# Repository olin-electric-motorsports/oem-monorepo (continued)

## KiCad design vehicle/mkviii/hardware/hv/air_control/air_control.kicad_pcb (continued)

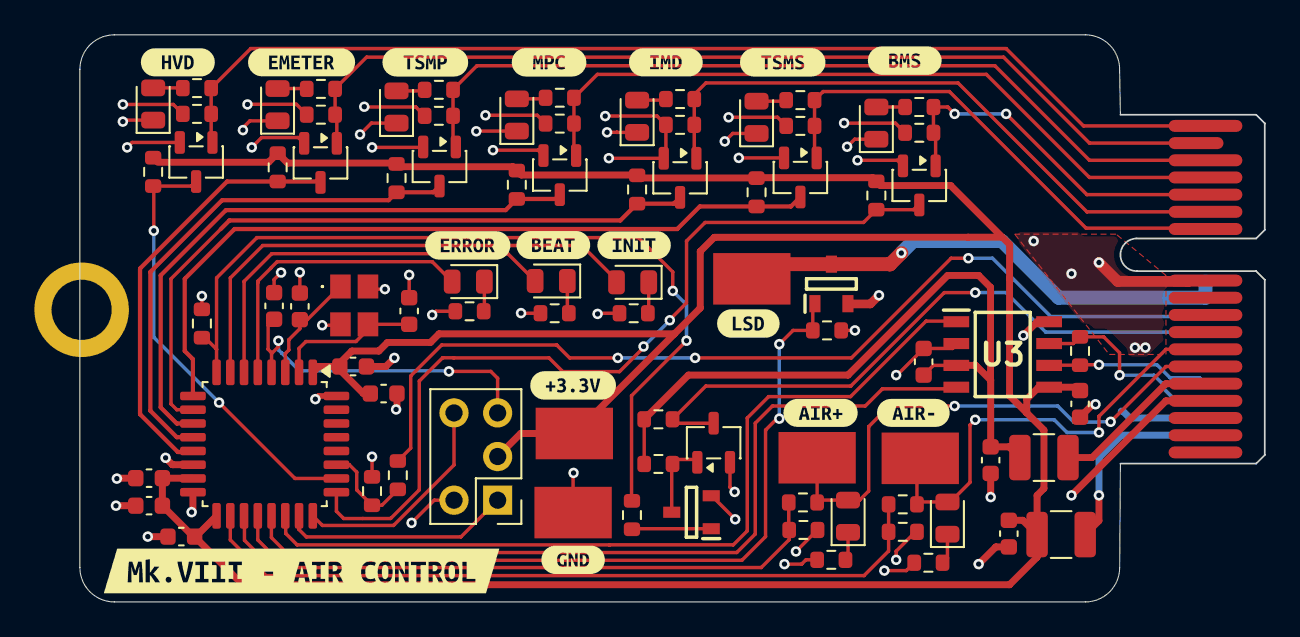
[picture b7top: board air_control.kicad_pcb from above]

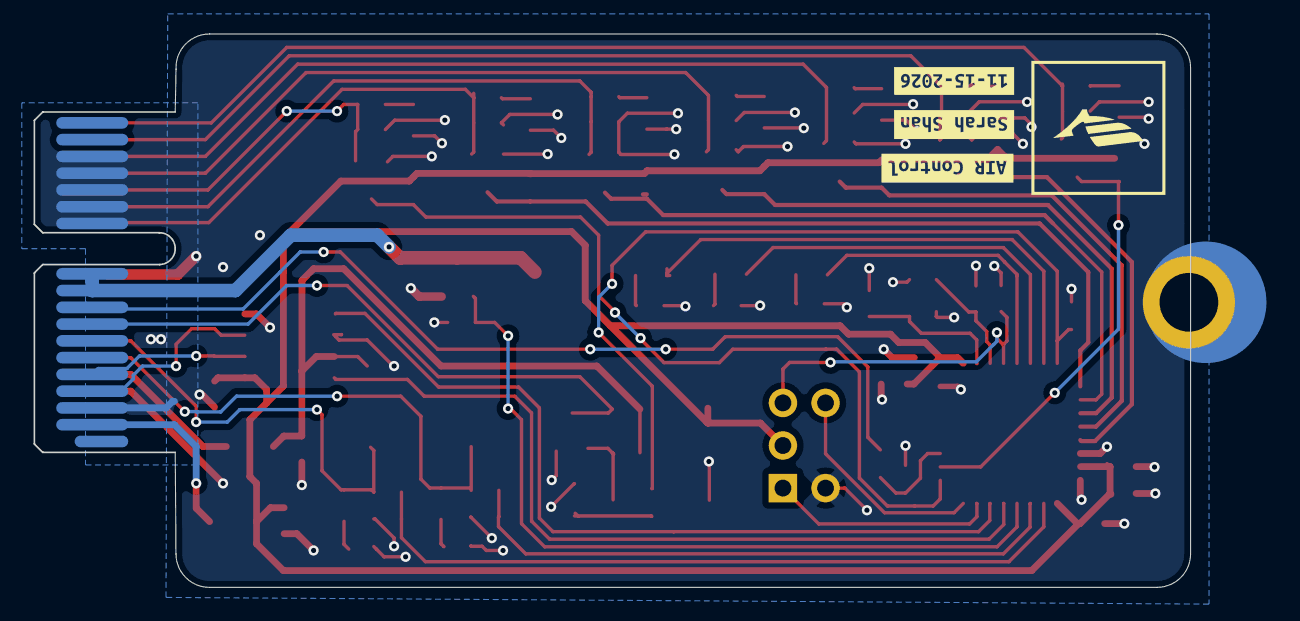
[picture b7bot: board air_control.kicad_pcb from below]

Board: 2 copper layers, 68.9 x 33.0 mm, 104 parts (3 on the bottom side), 55 nets.

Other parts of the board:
kibuzzard-6AF9317E: G***; kibuzzard-6AF9317E
kibuzzard-6AFA4FF6: G***; kibuzzard-6AFA4FF6
kibuzzard-6AFA20AB: G***; kibuzzard-6AFA20AB
kibuzzard-6AFA20E3: G***; kibuzzard-6AFA20E3
kibuzzard-6AFA20FC: G***; kibuzzard-6AFA20FC
kibuzzard-6AFA21A2: G***; kibuzzard-6AFA21A2
kibuzzard-6AFA21B3: G***; kibuzzard-6AFA21B3
kibuzzard-6AFA22A9: G***; kibuzzard-6AFA22A9
kibuzzard-6AFA27BC: G***; kibuzzard-6AFA27BC
kibuzzard-6AFA208A: G***; kibuzzard-6AFA208A
kibuzzard-6AFA210D: G***; kibuzzard-6AFA210D
kibuzzard-6AFA219C: G***; kibuzzard-6AFA219C
kibuzzard-6AFA2118: G***; kibuzzard-6AFA2118
kibuzzard-6AFA2276: G***; kibuzzard-6AFA2276
kibuzzard-6AFA2289: G***; kibuzzard-6AFA2289
kibuzzard-6AFA2297: G***; kibuzzard-6AFA2297
kibuzzard-6AFA2756: G***; kibuzzard-6AFA2756
kibuzzard-6AFA2784: G***; kibuzzard-6AFA2784
kibuzzard-6AFDC125: G***; kibuzzard-6AFDC125

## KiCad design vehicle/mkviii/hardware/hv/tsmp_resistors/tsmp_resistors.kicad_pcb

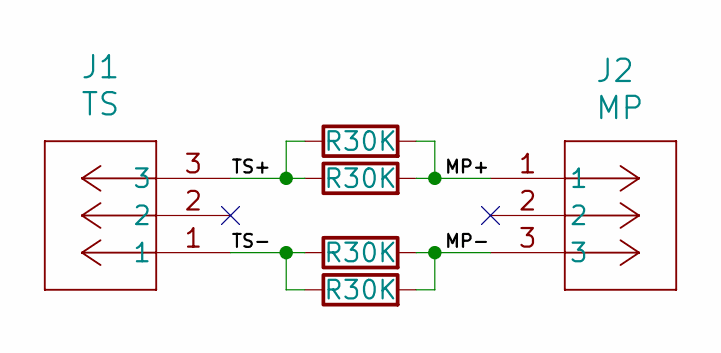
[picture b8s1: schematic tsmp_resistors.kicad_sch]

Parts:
J1: TS; J_Molex_Header_01x03_VT
J2: MP; J_Molex_Header_01x03_VT
R1, R2, R3, R4: R30K; R_5329_13573Metric; MPN SMF530KJT

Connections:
/MP+: J2.1, R1.2, R2.2
/MP-: J2.3, R3.2, R4.2
/TS+: J1.3, R1.1, R2.1
/TS-: J1.1, R3.1, R4.1

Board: 2 copper layers, 9 parts (3 on the bottom side), 4 nets, no tracks yet.

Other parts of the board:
kibuzzard-6B01073E: G***; kibuzzard-6B01073E
kibuzzard-6B01079E: G***; kibuzzard-6B01079E
kibuzzard-6B010778: G***; kibuzzard-6B010778

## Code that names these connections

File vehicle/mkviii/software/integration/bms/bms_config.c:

#include "bms_config.h"
#include "stm32g4xx_hal_tim.h"

TIM_HandleTypeDef htim2; // Fan PWM

/*
 * PIN DEFINITIONS
 */
// GPIO Setup
void GpioInit(void){
    // enable clocks for ports we are using
    __HAL_RCC_GPIOA_CLK_ENABLE();
    __HAL_RCC_GPIOB_CLK_ENABLE();

    // generic structure
    GPIO_InitTypeDef GPIO_InitStruct = {0};

    // port A outputs: relay drive and LEDs
    HAL_GPIO_WritePin(GPIOA, BMS_RELAY_DRIVE_PIN | HEARTBEAT_PIN | ERROR_LED_PIN | CSC_COMMS_PIN, GPIO_PIN_RESET);
    GPIO_InitStruct.Pin = BMS_RELAY_DRIVE_PIN | HEARTBEAT_PIN | ERROR_LED_PIN | CSC_COMMS_PIN;
    GPIO_InitStruct.Mode = GPIO_MODE_OUTPUT_PP;
    GPIO_InitStruct.Pull = GPIO_NOPULL;
    GPIO_InitStruct.Speed = GPIO_SPEED_FREQ_LOW;
    HAL_GPIO_Init(GPIOA, &GPIO_InitStruct);

    // configure port A inputs
    // BSPD_CURRENT_THRESH (PA9), driven by U7 so no pull needed
    GPIO_InitStruct.Pin = BSPD_CURRENT_THRESH_PIN;
    GPIO_InitStruct.Mode = GPIO_MODE_INPUT;
    GPIO_InitStruct.Pull = GPIO_NOPULL;
    HAL_GPIO_Init(BSPD_CURRENT_THRESH_PORT, &GPIO_InitStruct);

    // Fan PWM (PA0) is TIM2_CH1
    GPIO_InitStruct.Pin = FAN_PWM_PIN;
    GPIO_InitStruct.Mode = GPIO_MODE_AF_PP;
    GPIO_InitStruct.Pull = GPIO_NOPULL;
    GPIO_InitStruct.Speed = GPIO_SPEED_FREQ_LOW;
    GPIO_InitStruct.Alternate = GPIO_AF1_TIM2;
    HAL_GPIO_Init(FAN_PWM_PORT, &GPIO_InitStruct);

    // ISO_CS (PA15) and the SPI1 pins (PB3-PB5) are set up by oem_spi_init()
}

// timer initialization
void TimerInit(void) {
    // --- Timer 2: 25kHz fan PWM on CH1 ---
    // The 10ms main loop runs off HAL_GetTick() instead of a timer interrupt
    // because common/startup.c's vector table has no peripheral IRQ entries.
    __HAL_RCC_TIM2_CLK_ENABLE();

    htim2.Instance = TIM2;
    htim2.Init.Prescaler = 0;
    htim2.Init.CounterMode = TIM_COUNTERMODE_UP;
    htim2.Init.Period = (HAL_RCC_GetPCLK1Freq() / FAN_PWM_FREQ_HZ) - 1;
    htim2.Init.ClockDivision = TIM_CLOCKDIVISION_DIV1;
    htim2.Init.AutoReloadPreload = TIM_AUTORELOAD_PRELOAD_ENABLE;
    HAL_TIM_PWM_Init(&htim2);

    TIM_OC_InitTypeDef sConfigOC = {0};
    sConfigOC.OCMode = TIM_OCMODE_PWM1;
    sConfigOC.Pulse = 0;
    sConfigOC.OCPolarity = TIM_OCPOLARITY_HIGH;
    sConfigOC.OCFastMode = TIM_OCFAST_DISABLE;
    HAL_TIM_PWM_ConfigChannel(&htim2, &sConfigOC, TIM_CHANNEL_1);
}

// FDCAN1 on PA11 (RX) / PA12 (TX). Called by HAL_FDCAN_Init() from the
// generated can_init_bms(). The generated bit timing assumes the FDCAN kernel
// clock is the 16MHz HSE, which is the reset default.
void HAL_FDCAN_MspInit(FDCAN_HandleTypeDef* hfdcan) {
    if (hfdcan->Instance == FDCAN1) {
        __HAL_RCC_FDCAN_CLK_ENABLE();
        __HAL_RCC_GPIOA_CLK_ENABLE();

        GPIO_InitTypeDef GPIO_InitStruct = {0};
        GPIO_InitStruct.Pin = GPIO_PIN_11 | GPIO_PIN_12;
        GPIO_InitStruct.Mode = GPIO_MODE_AF_PP;
        GPIO_InitStruct.Pull = GPIO_NOPULL;
        GPIO_InitStruct.Speed = GPIO_SPEED_FREQ_LOW;
        GPIO_InitStruct.Alternate = GPIO_AF9_FDCAN1;
        HAL_GPIO_Init(GPIOA, &GPIO_InitStruct);
    }
}

// Defined in the generated can_api.c
extern FDCAN_HandleTypeDef hfdcan1;

void can_wait_for_tx_slot(void) {
    uint32_t start = HAL_GetTick();
    while (HAL_FDCAN_GetTxFifoFreeLevel(&hfdcan1) == 0
           && (HAL_GetTick() - start) < 2) {
    }
}

// interupt handlers
void SysTick_Handler(void) {
    HAL_IncTick(); // Critical for HAL_Delay() and HAL_GetTick() to work!
}

// ISO_CS is PA15, SPI1 is PB3 (SCK), PB4 (MISO), PB5 (MOSI).
// The LTC6820 has POL = PHA = 1 (SPI mode 3, matches common/spi) and SLOW = 0,
// so SCK must stay at or below 1MHz: 64MHz / 128 = 500kHz.
oem_spi_config_t bms_spi = {
    .spi_instance = SPI1,
    .cs_port = ISO_CS_PORT,
    .cs_pin = ISO_CS_PIN,
    .baud_prescaler = SPI_BAUDRATEPRESCALER_128
};

// ADC CONFIGURATION

// Current sensor output, divided down by R2/R4, on PA4 (ADC2_IN17)
oem_adc_config_t current_sense_vout = {
    .adc_instance = ADC2,
    .port = VOUT_CURRENT_SENSE_PORT,
    .pin = VOUT_CURRENT_SENSE_PIN,
    .channel = ADC_CHANNEL_17,
    .sample_time = ADC_SAMPLETIME_47CYCLES_5
};

cell_data_s cell_data = {0};

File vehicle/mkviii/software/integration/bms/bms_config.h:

#pragma once

#include <stdbool.h>       // For bool, true, false
#include <stdint.h>        // For uint8_t, int16_t, etc.
#include "stm32g4xx_hal.h" // The master STM32 HAL header

#include "common/adc/adc.h"
#include "common/spi/spi.h"

#include "vehicle/common/adbms1818/ADBMS181x.h"

// Pin Defs
// Taken from the U10 pads in hardware/integration/bms_core/bms_core.kicad_pcb
// (STM32G441KBT6, LQFP-32). PA1-PA3, PA10, PB0 and PB6-PB8 are unconnected.
// Port A
#define FAN_PWM_PIN              GPIO_PIN_0  // pin 5,  TIM2_CH1 (AF1)
#define FAN_PWM_PORT             GPIOA
#define VOUT_CURRENT_SENSE_PIN   GPIO_PIN_4  // pin 9,  ADC2_IN17, via 5.1k/10k divider
#define VOUT_CURRENT_SENSE_PORT  GPIOA
#define ERROR_LED_PIN            GPIO_PIN_5  // pin 10, red LED D3
#define ERROR_LED_PORT           GPIOA
#define CSC_COMMS_PIN            GPIO_PIN_6  // pin 11, green LED D2
#define CSC_COMMS_PORT           GPIOA
#define HEARTBEAT_PIN            GPIO_PIN_7  // pin 12, amber LED D1
#define HEARTBEAT_PORT           GPIOA
#define BMS_RELAY_DRIVE_PIN      GPIO_PIN_8  // pin 18, gate of Q1
#define BMS_RELAY_DRIVE_PORT     GPIOA
#define BSPD_CURRENT_THRESH_PIN  GPIO_PIN_9  // pin 19, output of U7
#define BSPD_CURRENT_THRESH_PORT GPIOA
#define ISO_CS_PIN               GPIO_PIN_15 // pin 25, LTC6820 ~CS
#define ISO_CS_PORT              GPIOA

// Port B
// ISO_SCK (PB3), ISO_MISO (PB4), ISO_MOSI (PB5) are SPI1 and are configured by
// oem_spi_init() in common/spi. Do not use PB3 as a GPIO.

extern TIM_HandleTypeDef htim2; // Fan PWM
#define FAN_PWM_FREQ_HZ (25000)

void TimerInit(void); // Function prototype to set them up

/*
 * Wait (up to 2ms) for a free slot in the FDCAN TX FIFO. The FIFO only holds 3
 * frames, so call this before each can_send_*() when sending several messages
 * back to back.
 */
void can_wait_for_tx_slot(void);

/*
 * Macros
 */
#define NUM_ICS          1

#define MAX_EXTRANEOUS_TEMPERATURES 3 // causing isssssueeeess... maybe set to higher value - ian W 9/14/2024
#define MAX_PEC_ERROR_COUNT \
    32 // copied from mkv where it still says arbitrary...

// copied from MKV - need to be updated
#define FAKE_DA_FIRE_BODGE                 ((int16_t)700) // 140 degC
#define OVERTEMPERATURE_THRESHOLD          ((int16_t)5725) // 60 degC
#define SOFT_OVERTEMPERATURE_THRESHOLD     ((int16_t)8892) // 45 degC
#define SOFT_OVERTEMPERATURE_THRESHOLD_LOW ((int16_t)11708) // 35 degC
#define UNDERTEMPERATURE_THRESHOLD         ((int16_t)27605) // -20 degC

// Cell voltage codes are in units of 100uV
#define OVERVOLTAGE_THRESHOLD          (42000) // 4.2V
#define UNDERVOLTAGE_THRESHOLD         (25000) // 2.5V (Li-ion chemistry minimum)
#define SEGMENT_OVERVOLTAGE_THRESHOLD  (714000) // 71.4V (4.2v * 17 cells)
#define SEGMENT_UNDERVOLTAGE_THRESHOLD (442000) // 44.2V (4.6 * 17 cells)

#define CURRENT_THRESH (12000) // 120A (peak current) * 100cA/A = 12,000 centiAmps

/*
 * Current sensor calibration. The sensor output (0-5V) goes through a
 * 5.1k/10k divider into PA4, so the sensor voltage is V_pin * 15.1 / 10.
 * CURRENT_SENSE_ZERO_MV is the sensor output at 0A. 2773mV is the zero point
 * MKVII used (raw 568 on a 10-bit, 5V ADC) - measure it on this car with no
 * current flowing and update.
 */
#define CURRENT_SENSE_ZERO_MV  (2773)
#define CURRENT_SENSE_MV_PER_A (20)

// Open wire: a cell is open if (pull-up reading - pull-down reading) is above
// this, in 100uV units. 4000 = 400mV, from the ADBMS181x reference driver.
#define OPEN_WIRE_THRESHOLD (4000)

// Cell balancing config
// Balance any cell more than this above the lowest cell (100uV units)
#define BALANCE_THRESHOLD (100) // 10mV
// Discharge timeout written to DCTO in CFGRA. Balancing switches turn off on
// their own if the BMS stops refreshing the config (0x1 = 0.5 minutes)
#define BALANCE_DCTO (0x1)

// ADBMS1818 internal die temperature, ITMP code in 100uV units.
// T(degC) = ITMP * 100uV / 7.6mV - 276, so 85degC -> (85 + 276) * 76 = 27436
#define DIE_OVERTEMPERATURE_THRESHOLD (27436)

// Number (out of 18) voltage channels not used. Unused channels are bridged
// and read as 0V
#define NUM_UNUSED_VOLTAGE_CHANNELS 1

/*
 * PIN & PERIPHERAL DEFINITIONS
 */
void GpioInit(void);

// 04/13/26
//SPI Peripheral Configuration
extern oem_spi_config_t bms_spi;

/** 04/18/26
 * ADC Configurations
 * Mapped to the STM32G4 ADC
 */
extern oem_adc_config_t current_sense_vout; // Mapped to PA4

// A little bit of a hacky, truncated version of the cell_asic
// struct defined by the LTC681X library. Filled by voltage_task() and used for
// cell balancing.
typedef struct {
    ic_register config;
    cv cells;
} cell_asic_trunc;

typedef struct {
    cell_asic_trunc cells[NUM_ICS];
} cell_data_s;

extern cell_data_s cell_data;

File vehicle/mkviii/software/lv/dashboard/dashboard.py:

###### DO NOT USE THIS CODE ######
#UPLOAD SCRIPT FROM THE CAR


import os
import threading
import time
import cantools
import can
import RPi.GPIO as GPIO

BUSTYPE = "socketcan"
CHANNEL = "can0"
BITRATE = 500000

# Loading in everyone's compiled config files
# (mkvi.dbc is deployed next to this file, see deploy/config.json)
dbc_file = os.path.join(os.path.dirname(os.path.abspath(__file__)), "mkvi.dbc")
db = cantools.database.load_file(dbc_file)

# Making variables that store incoming CAN data global
air_state = "INIT"
imd_status = "IMD OK"
bms_state = "ACTIVE"
brake_gate = "Brakelight OFF"
throttle_pressed = False

# Pin Definitions
BMS_LED_LSD = 36
HV_LED_LSD = 29
IMD_LED_LSD = 16  # 26 IAN W changing this 6/9/24
RTD_BUZZER_LSD = 32

RTD_BUTTON_SENSE = 31
BOTS_SHDN_SENSE = 18
E_STOP_SHDN_SENSE = 22

RTD_BUTTON_LED = 33
PROGRAMMING_LED_1 = 40
PROGRAMMING_LED_2 = 38
PROGRAMMING_LED_3 = 37

# Number of seconds the buzzer sounds
RTD_BUZZ_TIME = 2000  # in milliseconds

# Initializing the dictionary that holds outgoing CAN data
dashboard_data = {"ready_to_drive": False, "start_button_state": False, "ss_estop": False, "ss_bots": False, }


def init_can(channel, bustype, bitrate, callback):
    """Initialize CAN hardware and create CAN database from DBC
    Args:
        channel: port or network interface on the
                 Raspi the CAN single is connected to
        bustype: Type of CAN interface/dongle
        bitrate: Bus speed in Kbps

    """
    can_bus = can.interface.Bus(
        channel=channel,
        bustype=bustype,
        bitrate=bitrate,
    )

    kill_flag = threading.Event()
    listener = threading.Thread(
        target=dashboard_listener,
        name="listener",
        kwargs={"can_bus": can_bus, "callback": callback, "kill_flag": kill_flag},
    )

    listener.start()
    return can_bus, kill_flag


def dashboard_listener(can_bus, callback, kill_flag):
    """Thread that runs all the time to listen to CAN messages
    References:
      - https://python-can.readthedocs.io/en/master/interfaces/socketcan.html
      - https://python-can.readthedocs.io/en/master/
    """
    while not kill_flag.is_set():
        msg = can_bus.recv(1)  # 1 second receive timeout
        if msg:
            callback(msg, db)

    can_bus.shutdown()
    print("Exited gracefully")


def dashboard_callback(msg, db):
    """
    Callback when a CAN message is received, updates appropriate vehicle
    dictionaries
    Args:
        msg (can.Message): CAN message that was received
        db (cantools.database): Database generated from our DBC
    """
    global air_state, imd_status, bms_state, brake_gate, throttle_pressed

    try:
        message = db.decode_message(msg.arbitration_id, msg.data)
    except Exception as _:
        print("bad message")
        return

    message_name = db.get_message_by_frame_id(msg.arbitration_id).name

    if message_name == "air_control_critical":
        air_state = message.get("air_state")
        imd_status = message.get("imd_status")
    if message_name == "bms_core":
        bms_state = message.get("bms_state")
        print(bms_state)
    if message_name == "bspd":
        brake_gate = message.get("brake_gate") == "Brakelight ON"
    if message_name == "throttle":
        throttle_l = message.get("throttle_l_pos")
        throttle_r = message.get("throttle_r_pos")
        throttle_pressed = throttle_l >= 12 or throttle_r >= 12


# Enabling the start button interrupt
def button_pressed_callback(channel):
    """
    When called, this sets the value of "start_button_state" in the outgoing
    CAN data dictionary (dashboard_data) to True
    """
    dashboard_data["start_button_state"] = GPIO.input(RTD_BUTTON_SENSE)


def shutdown_callback(channel):
    """
    When called, this updates the values of "ss_bots" and "ss_estop" in the
    outgoing CAN data dictionary (dashboard_data) to False

    Args:
        channel: an integer representing a pin number corresponding to either
        the ss_bots or ss_estop pins
    """
    if channel == BOTS_SHDN_SENSE:
        dashboard_data["ss_bots"] = GPIO.input(BOTS_SHDN_SENSE)
    if channel == E_STOP_SHDN_SENSE:
        dashboard_data["ss_estop"] = GPIO.input(E_STOP_SHDN_SENSE)


def main():
    """
    Contains the superloop intended to run every 10 milliseconds;
    Separate thread continually updates relevant variables
    `dashboard_data` is a dictionary containing all outgoing CAN data.
    """
    # Set pin numbering system
    GPIO.setmode(GPIO.BOARD)

    # Channel Setup/Pin Mode Setup
    channel_outputs = [
        BMS_LED_LSD,
        HV_LED_LSD,
        IMD_LED_LSD,
        RTD_BUZZER_LSD,
        RTD_BUTTON_LED,
        PROGRAMMING_LED_1,
        PROGRAMMING_LED_2,
        PROGRAMMING_LED_3,
    ]

    channel_inputs = [RTD_BUTTON_SENSE, BOTS_SHDN_SENSE, E_STOP_SHDN_SENSE]
    GPIO.setup(channel_outputs, GPIO.OUT)
    GPIO.setup(channel_inputs, GPIO.IN)
    GPIO.output(HV_LED_LSD, 1)
    GPIO.output(IMD_LED_LSD, 1)
    GPIO.output(BMS_LED_LSD, 1)
    time.sleep(.5)
    GPIO.output(HV_LED_LSD, 0)
    GPIO.output(IMD_LED_LSD, 0)
    GPIO.output(BMS_LED_LSD, 0)
    # Initialize a thread to constantly update STATES_DICTIONARY from CAN messages
    can_bus, kill_flag = init_can(CHANNEL, BUSTYPE, BITRATE, dashboard_callback)

    # Adding start button, bots shutdown, and estop shutdown interrupts
    GPIO.add_event_detect(
        RTD_BUTTON_SENSE, GPIO.BOTH, callback=button_pressed_callback, bouncetime=50
    )
    GPIO.add_event_detect(BOTS_SHDN_SENSE, GPIO.RISING, callback=shutdown_callback)
    GPIO.add_event_detect(E_STOP_SHDN_SENSE, GPIO.RISING, callback=shutdown_callback)
    #GPIO.output(IMD_LED_LSD, 1)
    buzzer_counter = 0  # buzzer_counter starts at 0

    dashboard_message = db.get_message_by_name("dashboard")

    button_pressed_callback(RTD_BUTTON_SENSE)
    shutdown_callback(BOTS_SHDN_SENSE)
    shutdown_callback(E_STOP_SHDN_SENSE)
    #GPIO.output(BMS_LED_LSD, 1)

    while True:  # MAKE THIS RUN EVERY 10 MILLISECONDS
        t_0 = time.perf_counter()

        # Turns on BMS LED if there are any BMS faults
        GPIO.output(PROGRAMMING_LED_1, bms_state != "ACTIVE")
        GPIO.output(BMS_LED_LSD, bms_state != "ACTIVE")

        # Turns on HV LED if the tractive system is on
        GPIO.output(HV_LED_LSD, air_state == "TS_ACTIVE")

        # Turns on IMD LED if there is an IMD fault; imd_status True is good
        GPIO.output(IMD_LED_LSD, imd_status != "IMD OK")

        # Turns on the button LED if brakes are pressed, tractive system is on,
        # RTD is not on, and the throttle is not being pressed
        if (
            brake_gate
            and air_state == "TS_ACTIVE"
            and not dashboard_data["ready_to_drive"]
            and not throttle_pressed
        ):
            GPIO.output(RTD_BUTTON_LED, 1)  # Turn on button LED
        else:
            GPIO.output(RTD_BUTTON_LED, 0)

        # Update "ready_to_drive", turn off the button LED and start the buzzer
        # Set the counter to 0 to start off with
        if (
            air_state == "TS_ACTIVE"
            and brake_gate
            and dashboard_data["start_button_state"]
            and not throttle_pressed
        ):
            dashboard_data["ready_to_drive"] = True
            GPIO.output(RTD_BUTTON_LED, 0)
            GPIO.output(RTD_BUZZER_LSD, 1)

        # Turn off the button LED and RTD false in dicts if tractive system not active
        # Also reset the buzzer
        if air_state != "TS_ACTIVE":
            GPIO.output(RTD_BUTTON_LED, 0)  # Turn off button LED
            dashboard_data["ready_to_drive"] = False
            buzzer_counter = 0

        # Add 10 milliseconds to the buzzing timer every loop
        if dashboard_data["ready_to_drive"] and buzzer_counter < RTD_BUZZ_TIME:
            buzzer_counter += 10

        if buzzer_counter >= RTD_BUZZ_TIME:
            GPIO.output(RTD_BUZZER_LSD, 0)

        data = dashboard_message.encode(dashboard_data)
        message = can.Message(arbitration_id=dashboard_message.frame_id, data=data, is_extended_id=False)
        can_bus.send(message)  # Send out RTD status over CAN
        
        # Make the loop run every 10 milliseconds
        delta = time.perf_counter() - t_0
        if delta < 0.01:
            time.sleep(0.01 - delta)


# Stores code that should only run when dashboard.py is run as a script and not
# as a module
if __name__ == "__main__":
    main()

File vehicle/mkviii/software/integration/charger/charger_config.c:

#include "charger.h"

/*
 * =========================
 * Timer handle
 * =========================
 */
TIM_HandleTypeDef htim2;

/*
 * =========================
 * SPI configs
 * =========================
 *
 * LCD:
 *   CS   = PA15
 *   SCK  = PB3
 *   MISO = PB4
 *   MOSI = PB5
 *
 * Charger CAN controller:
 *   CS   = PB12
 *   SCK  = PB13
 *   MISO = PB14
 *   MOSI = PB15
 */
oem_spi_config_t lcd_spi = {
    .spi_instance = SPI1,
    .cs_port = LCD_SPI_CS_GPIO_Port,
    .cs_pin = LCD_SPI_CS_Pin,
    .baud_prescaler = SPI_BAUDRATEPRESCALER_16
};

oem_spi_config_t charger_spi = {
    .spi_instance = SPI2,
    .cs_port = CAN_CTRLR_SPI_CS_GPIO_Port,
    .cs_pin = CAN_CTRLR_SPI_CS_Pin,
    .baud_prescaler = SPI_BAUDRATEPRESCALER_64
};

/*
 * If your STM32 MCP25625 wrapper needs this object, uncomment and adapt as needed.
 *
MCP25625 charger_CAN_converter = {
    .speed = 250000,
    .spi_struct = &charger_spi,
    .rst = &(gpio_t){0},
    .stby = &(gpio_t){0}
};
*/

void GpioInit(void) {
    /*
    __HAL_RCC_GPIOA_CLK_ENABLE();
    __HAL_RCC_GPIOB_CLK_ENABLE();
    __HAL_RCC_GPIOC_CLK_ENABLE();
    */

    GPIO_InitTypeDef GPIO_InitStruct = {0};

    /*
     * =========================
     * Status / control output pins
     * =========================
     */
    HAL_GPIO_WritePin(SPI_STATUS_GPIO_Port, SPI_STATUS_Pin, GPIO_PIN_RESET);
    HAL_GPIO_WritePin(CHARGING_STATUS_GPIO_Port, CHARGING_STATUS_Pin, GPIO_PIN_RESET);
    HAL_GPIO_WritePin(FULLY_CHARGED_STATUS_GPIO_Port, FULLY_CHARGED_STATUS_Pin, GPIO_PIN_RESET);
    HAL_GPIO_WritePin(ELCON_READY_GPIO_Port, ELCON_READY_Pin, GPIO_PIN_RESET);
    HAL_GPIO_WritePin(CAR_READY_GPIO_Port, CAR_READY_Pin, GPIO_PIN_RESET);
    HAL_GPIO_WritePin(CHARGING_ON_OFF_STATUS_GPIO_Port, CHARGING_ON_OFF_STATUS_Pin, GPIO_PIN_RESET);
    HAL_GPIO_WritePin(CAN_STATUS_GPIO_Port, CAN_STATUS_Pin, GPIO_PIN_RESET);
    HAL_GPIO_WritePin(HEARTBEAT_GPIO_Port, HEARTBEAT_Pin, GPIO_PIN_RESET);

    /*
     * Port A outputs
     */
    GPIO_InitStruct.Pin = SPI_STATUS_Pin |
                          CHARGING_STATUS_Pin |
                          FULLY_CHARGED_STATUS_Pin |
                          ELCON_READY_Pin |
                          CAR_READY_Pin |
                          CHARGING_ON_OFF_STATUS_Pin |
                          EVSE_PWM_Pin;
    GPIO_InitStruct.Mode = GPIO_MODE_OUTPUT_PP;
    GPIO_InitStruct.Pull = GPIO_NOPULL;
    GPIO_InitStruct.Speed = GPIO_SPEED_FREQ_LOW;
    HAL_GPIO_Init(GPIOA, &GPIO_InitStruct);

    /*
     * Port C outputs
     */
    GPIO_InitStruct.Pin = CAN_STATUS_Pin | HEARTBEAT_Pin;
    GPIO_InitStruct.Mode = GPIO_MODE_OUTPUT_PP;
    GPIO_InitStruct.Pull = GPIO_NOPULL;
    GPIO_InitStruct.Speed = GPIO_SPEED_FREQ_LOW;
    HAL_GPIO_Init(GPIOC, &GPIO_InitStruct);

    /*
     * =========================
     * LCD control pins
     * CS = PA15
     * RST = PB6
     * BLK = PB7
     * =========================
     */


     /*
    HAL_GPIO_WritePin(LCD_SPI_CS_GPIO_Port, LCD_SPI_CS_Pin, GPIO_PIN_SET);
    HAL_GPIO_WritePin(LCD_RST_GPIO_Port, LCD_RST_Pin, GPIO_PIN_SET);
    HAL_GPIO_WritePin(LCD_BLK_GPIO_Port, LCD_BLK_Pin, GPIO_PIN_SET);
    */


    /*
     * LCD CS on PA15
     */
    GPIO_InitStruct.Pin = LCD_SPI_CS_Pin;
    GPIO_InitStruct.Mode = GPIO_MODE_OUTPUT_PP;
    GPIO_InitStruct.Pull = GPIO_NOPULL;
    GPIO_InitStruct.Speed = GPIO_SPEED_FREQ_HIGH;
    HAL_GPIO_Init(GPIOA, &GPIO_InitStruct);

    GPIO_InitStruct.Pin = LCD_RST_Pin | LCD_BLK_Pin;
    GPIO_InitStruct.Mode = GPIO_MODE_OUTPUT_PP;
    GPIO_InitStruct.Pull = GPIO_NOPULL;
    GPIO_InitStruct.Speed = GPIO_SPEED_FREQ_HIGH;
    HAL_GPIO_Init(GPIOB, &GPIO_InitStruct);

    HAL_GPIO_WritePin(CAN_CTRLR_SPI_CS_GPIO_Port, CAN_CTRLR_SPI_CS_Pin, GPIO_PIN_SET);
    HAL_GPIO_WritePin(CAN_CTRLR_RST_GPIO_Port, CAN_CTRLR_RST_Pin, GPIO_PIN_SET);
    HAL_GPIO_WritePin(CHARGER_STBY_GPIO_Port, CHARGER_STBY_Pin, GPIO_PIN_RESET);

    GPIO_InitStruct.Pin = CAN_CTRLR_RST_Pin | CAN_CTRLR_SPI_CS_Pin;
    GPIO_InitStruct.Mode = GPIO_MODE_OUTPUT_PP;
    GPIO_InitStruct.Pull = GPIO_NOPULL;
    GPIO_InitStruct.Speed = GPIO_SPEED_FREQ_HIGH;
    HAL_GPIO_Init(GPIOB, &GPIO_InitStruct);

    GPIO_InitStruct.Pin = CHARGER_STBY_Pin;
    GPIO_InitStruct.Mode = GPIO_MODE_OUTPUT_PP;
    GPIO_InitStruct.Pull = GPIO_NOPULL;
    GPIO_InitStruct.Speed = GPIO_SPEED_FREQ_HIGH;
    HAL_GPIO_Init(GPIOA, &GPIO_InitStruct);

    GPIO_InitStruct.Pin = LCD_SPI_SCK_Pin | LCD_SPI_MISO_Pin | LCD_SPI_MOSI_Pin;
    GPIO_InitStruct.Mode = GPIO_MODE_AF_PP;
    GPIO_InitStruct.Pull = GPIO_NOPULL;
    GPIO_InitStruct.Speed = GPIO_SPEED_FREQ_VERY_HIGH;
    GPIO_InitStruct.Alternate = GPIO_AF5_SPI1;
    HAL_GPIO_Init(GPIOB, &GPIO_InitStruct);

    GPIO_InitStruct.Pin = CAN_CTRLR_SPI_SCK_Pin |
                          CAN_CTRLR_SPI_MISO_Pin |
                          CAN_CTRLR_SPI_MOSI_Pin;
    GPIO_InitStruct.Mode = GPIO_MODE_AF_PP;
    GPIO_InitStruct.Pull = GPIO_NOPULL;
    GPIO_InitStruct.Speed = GPIO_SPEED_FREQ_VERY_HIGH;
    GPIO_InitStruct.Alternate = GPIO_AF5_SPI2;
    HAL_GPIO_Init(GPIOB, &GPIO_InitStruct);

    GPIO_InitStruct.Pin = CAN_RX_Pin | CAN_TX_Pin;
    GPIO_InitStruct.Mode = GPIO_MODE_AF_PP;
    GPIO_InitStruct.Pull = GPIO_NOPULL;
    GPIO_InitStruct.Speed = GPIO_SPEED_FREQ_VERY_HIGH;
    GPIO_InitStruct.Alternate = GPIO_AF9_FDCAN1;
    HAL_GPIO_Init(GPIOA, &GPIO_InitStruct);
}

void TimerInit(void) {
    __HAL_RCC_TIM2_CLK_ENABLE();

    htim2.Instance = CHARGER_MAIN_TIM_INSTANCE;
    htim2.Init.Prescaler = 15999;      /* 16 MHz / 16000 = 1 kHz */
    htim2.Init.CounterMode = TIM_COUNTERMODE_UP;
    htim2.Init.Period = 9;             /* 1 kHz / 10 = 100 Hz => 10 ms */
    htim2.Init.ClockDivision = TIM_CLOCKDIVISION_DIV1;
    htim2.Init.AutoReloadPreload = TIM_AUTORELOAD_PRELOAD_ENABLE;
    HAL_TIM_Base_Init(&htim2);

    HAL_NVIC_SetPriority(TIM2_IRQn, 0, 0);
    HAL_NVIC_EnableIRQ(TIM2_IRQn);
    HAL_TIM_Base_Start_IT(&htim2);
}

void TIM2_IRQHandler(void) {
    HAL_TIM_IRQHandler(&htim2);
}

void SysTick_Handler(void) {
    HAL_IncTick();
}

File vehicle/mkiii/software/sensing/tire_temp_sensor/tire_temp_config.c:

#include "tire_temp.h"


void SysTick_Handler(void) {
  HAL_IncTick();
}
static void GpioInit(void) {
  __HAL_RCC_GPIOF_CLK_ENABLE();
  __HAL_RCC_GPIOA_CLK_ENABLE();

  GPIO_InitTypeDef GPIO_InitStruct = {0};

  /*// Uses PA1_... from throttle.h
  HAL_GPIO_WritePin(SDA_PORT, SDA_PIN, GPIO_PIN_RESET);

  GPIO_InitStruct.Pin = SDA_PIN;
  GPIO_InitStruct.Mode = GPIO_MODE_OUTPUT_PP;
  GPIO_InitStruct.Pull = GPIO_PULLUP;
  GPIO_InitStruct.Speed = GPIO_SPEED_FREQ_HIGH;
  HAL_GPIO_Init(SDA_PORT, &GPIO_InitStruct);

  HAL_GPIO_WritePin(SCL_PORT, SCL_PIN, GPIO_PIN_RESET);
  GPIO_InitStruct.Pin = SCL_PIN;
  GPIO_InitStruct.Mode = GPIO_MODE_OUTPUT_PP;
  GPIO_InitStruct.Pull = GPIO_PULLUP;
  GPIO_InitStruct.Speed = GPIO_SPEED_FREQ_HIGH;
  HAL_GPIO_Init(SDA_PORT, &GPIO_InitStruct);*/
  //defining heartbeat pin
  HAL_GPIO_WritePin(HEARTBEAT_LED_PORT, HEARTBEAT_LED_PIN, GPIO_PIN_RESET);
  GPIO_InitStruct.Pin = HEARTBEAT_LED_PIN;
  GPIO_InitStruct.Mode = GPIO_MODE_OUTPUT_PP;
  GPIO_InitStruct.Pull = GPIO_NOPULL;
  GPIO_InitStruct.Speed = GPIO_SPEED_FREQ_LOW;
  HAL_GPIO_Init(HEARTBEAT_LED_PORT, &GPIO_InitStruct);
  
  //define debug LED
  
  HAL_GPIO_WritePin(DEBUG_LED_PORT, DEBUG_LED_PIN, GPIO_PIN_RESET);
  GPIO_InitStruct.Pin = DEBUG_LED_PIN;
  GPIO_InitStruct.Mode = GPIO_MODE_OUTPUT_PP;
  GPIO_InitStruct.Pull = GPIO_PULLDOWN;
  GPIO_InitStruct.Speed = GPIO_SPEED_FREQ_HIGH;
  HAL_GPIO_Init(DEBUG_LED_PORT, &GPIO_InitStruct);

}

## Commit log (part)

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2026-03-17 Added production files; rounded corners; added throttle power wire terminal
2026-03-17 importated cantool and will begin to work on DBC generation
2026-03-18 Prechrarge Discharge - Schematic Organized
2026-03-18 fully functioning dbc generator
2026-03-19 Added Onboarding Related Files
2026-03-20 Everything builds but there is no testing done yet, so now is just testing
2026-03-21 Correctly sending CAN messages but not recieving them from other boards on the CAR
2026-03-21 fully tested and integrated system for CAN, will need file clean up tho but everything is proven to work
2026-03-22 reorganized all the files into an easier way to merge things
2026-03-22 fixed all build errors
2026-03-23 fixed comments
2026-03-23 Formatting: rename example to blinky and move function implementations from source to header
2026-03-23 Small README changes
2026-03-23 CAN integration into the car with format changes
2026-03-27 Windows compatible repo
2026-03-31 Add adc lib first draft
2026-03-31 Add ADC library
2026-03-31 Add bazel files & update header documentation
2026-04-02 Add testing code for adc lib
2026-04-03 polish library and example code, ready to use
2026-04-04 Clean up of ADC library and fixed timing issues
2026-04-04 fixed build erros
2026-04-04 ADC library & example code
    Fully working ADC library to make using ADC pin easier. Also There was a sneaky fix for the clock so timing would actually be correct for everyones boards
2026-04-04 most up to data
2026-04-04 Final version of roadkill harness
2026-04-04 fixed error file
2026-04-04 Precharge-Discharge Board Schematics and PCB
2026-04-04 Update charging board integration
2026-04-04 Charging Board Schematics and PCB (#16)
2026-04-10 integrated sensor's api to help read sensor data. Got functions to read data, convert data into temperature, find average temperature, find the max temperature and find where that is. Also flags over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
2026-04-11 Fixed wrong resistor values for BMS DA SMBus; moved all files to the mkviii folder from mkiii
2026-04-11 Corrected Date on BMS DA Schematics
2026-04-11 Added Power-Thermistor PCB provided by Liam Fries with minor schematic changes (modified title block; added temperature sensor and connector)
2026-04-11 Added Production Files and updated PCB file to match PCB file used for production files.
2026-04-11 Power-Thermistor Schematics and PCB (#24)
2026-04-11 fixing files
2026-04-11 BMS Motherboard Schematics and PCB Layout (#19)
2026-04-11 fix file and bazel constrants
2026-04-11 initial setup for bms
2026-04-12 roadkill harness - 3 LED blinky code(works)
2026-04-12 can_api: Revise README for STM32 transition
2026-04-13 initial guess on how spi work but not tested
2026-04-13 untested SPI code
2026-04-13 untested new git hooks that fix rebasing issues
2026-04-14 commiting blinky code
2026-04-14 committing new bms_config.c and old bms_config.h
2026-04-14 Timer Blinky Example
2026-04-14 bms_config with SPI using jacob's example
2026-04-14 rkh - began yml and adding CAN
2026-04-14 Time to commit (VS Code saved my as*, huge thanks to Jacob K.)
2026-04-15 Power Therm overhall, have not been reviewed yet
2026-04-15 fixed suggested edits and moved connector
2026-04-16 Minor redcube schematic changes; added some silkscreen; added production files
2026-04-16 moved e-meter part and moved up GND plane
2026-04-16 fixes for connector to BMS MOBO
2026-04-16 Adapted ADC code to oem library
2026-04-16 fixed a trace
2026-04-16 Modified 1-Wire Traces; Added Final Production Files
2026-04-18 BSPD code of VCU finished except CAN, along with some minor changes in Throttle code of VCU
2026-04-18 RKH - added input of PA4 pin (motor current)
2026-04-18 Precharge-discharge Renaming for BOM
2026-04-18 added pin defintions
2026-04-18 rkh - added CAN, Still need to debug CAN before flashing this code to my pcb
2026-04-18 Power-Therm (Rev. 2) and Git Hooks Script Changes (#25)
2026-04-21 I fixed the build errors (I did the exact same mistakes when doing the ADC lib)
2026-04-22 commiting bms timer implementation
2026-04-23 updated pin layout and charger files, yml file is filler for now
2026-04-23 added build file
2026-04-23 commented out some lcd code
2026-04-23 commented out all LCD aspects, builds succesfully
2026-04-23 Changed some minor software things but at this point I am like 90% sure it is hardware issue
2026-04-24 rkh - firmware done, ready for debugging!
2026-04-25 Commiting angle_sensor code and updating file paths.
2026-04-25 Committing initial angle_sensor code.
2026-04-25 Committing partially complete PWM capture code.
2026-04-25 added ADBMS support files and have new way of trying to communicat ISOSPI, still unable to recieve signals
2026-04-26 Add MCP25625 library
2026-04-26 spi is working but I cannot git values of IsoSpi but when I plug the MISO and MOSI on the STM it mirrors values so I'm guessing hardware issue
2026-04-27 commiting missing functions in bms.c based on mkvii and copied over tasks folder from mkvii
2026-04-27 CAN API: Update README
2026-04-27 CAN API: README Formatting
2026-04-27 CAN API README (#26)
2026-04-28 commiting utils folder
2026-04-30 most recent firmware
2026-04-30 Some changes during hardware testing
2026-05-01 Firmware update, CAN doesnt work at this stage, may or may not be my firmware
2026-05-02 Worked for 16s Merge BSPD and throttle VCU firmware
    Consolidate the separate BSPD and throttle VCU firmware into a single VCU
    target with shared GPIO, ADC, and runtime state.
    Add combined fault handling for APPS, brake/throttle implausibility, BSPD
    latch, BSPD shutdown sense, and inertia switch sense. Split shutdown-chain
    GPIO reads into vcu_read_shutdown_chain_1ms() and feed the resulting closed
    states into the fault manager.
2026-05-07 Merged Throttle and BSPD firmware, implemented CAN functions, ready to test
2026-05-08 lowkey not too sure what changed
2026-05-10 Updated VCU Kicad including both schematics and layout according to changes that had been made during hardware testing: removed R15, changed R14 to 0 ohm
2026-05-12 Added more comments (docstrings) to the code
2026-05-23 Updated KiCad Parts Library
2026-05-23 Removed Duplicate KiCad Files and kicad_wks file
2026-05-24 Standardized Folder Names
2026-05-24 Moved examples to example folder; removed outdated example
2026-05-24 Restored Working Version of Brake Temperature Sensor Project Schematics
2026-05-26 Fixed Path Error in Example DBC Generator BUILD File
2026-06-05 Replaced TO247.wrl with TO247.step 3D model to work well with Git LFS and associated changes
2026-06-06 Added OEM Info Footprint
2026-06-15 add .history folder to .gitignore
2026-06-15 Layout Draft 1
2026-06-22 Layout v2
2026-06-24 Layout Draft 3
2026-06-28 final tweeks
